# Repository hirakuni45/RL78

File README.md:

RL78
=========

[Japanese](READMEja.md)

## RL78 directories, overview, etc.

This is a program by RL78 and its compiler, rl78-elf-gcc,g++.
   
***For RL78 development, you can use the integrated development environment provided by Renesas Electronics, but for permanent use, you need to purchase the commercial version or generate your own.   
However, you need to purchase the commercial version to use it permanently, or you need to purchase the integrated development environment for RL78 because the generated binaries are limited to 64 Kbytes or less.   
Also, since it does not support C++, use gcc.   
We also emphasize the convenience of development on multiple platforms, such as Mac OS-X and Linux.   
I can also use [Open Source Tools for Renesas](https://llvm-gcc-renesas.com/)'s development tools, which require registration, but they don't fit my development style.   
I don't like IDEs very much. ***
   
Currently, I mainly provide headers, related libraries, etc. for "R5F100L" (G13 group).
   
R5F100LCAFB (FLASH: 32K, RAM: 2K, DATA-FLASH: 4K) @250 yen   
R5F100LEAFB (FLASH: 64K, RAM: 4K, DATA-FLASH:4K) @290 yen   
R5F100LGAFB (FLASH:128K, RAM:12K, DATA-FLASH:8K) @340 yen (conversion board already mounted @420 yen)   
R5F100LJAFB (FLASH:256K, RAM:20K, DATA-FLASH:8K) @400 yen   

@xxx is [reference price for Akizuki Denshi sales](http://akizukidenshi.com/catalog/c/crl78g13/)
   
The project consists of Makefile, related headers, and source code, and is composed of dedicated startup routines, linker scripts
It consists of a dedicated startup routine and a linker script.
Therefore, no dedicated boot program or loader is required, and the binaries you create can be executed as is.   
This means that you can run your application as is, without the need for a dedicated boot program or loader.
The entire process from the hardware reset to the device and your application running is detailed and easy to understand.   

***The most common case is that the compiler has been modified to switch functions dynamically, internally. ***   
***You can build a practical environment with only gcc and make without such a step. ***   
   
For device I/O operations, a template class library composed in C++ is used, and dedicated headers and class libraries for various devices are prepared.   
We are constantly improving and researching to realize highly functional and flexible operations with minimal implementation.   
We are looking for class libraries for unknown devices. (Must be able to provide under MIT license)   
E-Mail: hira@rvf-rc45.net

## RL78 Project List

|directory|contents|
|---|---|
|rl78prog|Programming tool to write programs to RL78 flash|
|G13|G13 group, linker scripts, device definition files|
|common|RL78 shared classes, small class library, utilities|
|chip|control classes for various devices, etc.||
|ff12a|"FatFS 0.12a" framework created by ChaN, and RL78/G13 SPI|
|KiCAD_Lib|Parts library for KiCAD|
|data_flah_lib|GR-Cotton/GR-Kurumi data/flash operation library|
|FIRST_sample|Super simple sample (blinking LED) for RL78/G13 devices|
|SOFT_DELAY_sample|Software timer sample for RL78/G13 devices|
|UART_sample|Serial communication sample for RL78/G13 devices|
|ARITH_sample|RL78/G13 Four arithmetic operations sample (receive and calculate mathematical expression by string)|
|ADC_sample|RL78/G13 internal A/D conversion sample|
|ADC_SWITCH_sample|RL78/G13 series switch (four rows) A/D conversion sample|
|THERMISTOR_sample|RL78/G13 Thermistor temperature display sample (using A/D conversion)|
|TOUCH_sample|RL78/G13 touch switch, sample|
|DATA_FLASH_sample|RL78/G13 Data flash sample (read, write, erase)
|INTERVAL_TIMER_sample|RL78/G13 internal 12-bit, interval timer samples|
|INTERVAL_TIMER_TAU_sample|RL78/G13 TAU use interval timer sample|
|EEPROM_sample|RL78?G13 EEPROM I2C Read/Write sample|
|DS3231_sample|RL78/G13 DS3231 I2C Real Time Clock time display and setting sample|
|DS1371_sample|RL78/G13 DS1371 I2C Real Time Clock time display, setting sample|
|BMP180_sample|RL78/G13 BMP180 I2C Pressure/Temperature sensor reading and display sample|
|VL53L0X_sample|RL78/G13 VL53L0X I2C Time-of-Flight distance sensor, sample|
|PWM_sample|RL78/G13 TAU use PWM output sample| 
|SDC_sample|RL78/G13 SD card operation sample (SD card root directory list)||
|WAV_PLAYER_sample|RL78/G13 WAV file playback sample (8-bit output by PWM modulation, up to 48KHz/16bits)
|VS1063_PLAYER_sample|RL78/G13 VS1063 Audio Decoder Playback sample
|LCD_DOT_sample|RL78/G13 ST7565(R)/SSD1306 SPI LCD controller, graphics display sample|
|MAX6675_sample|RL78/G13 MAX6675 SPI K thermocouple, temperature display sample|
|MAX7219_sample|RL78/G13 MAX7219 SPI LED display sample|

### Enable/Disable FatFS LFN   
The SD card file system "fatfs" uses "LFN" (long file name) as standard and displays UTF-8 is used as standard.    (UTF-8 and Shift-JIS conversion tables are available.)   
This requires a device of at least 128KB.   
This consumes a lot of memory. If you do not need it, set "_USE_LFN" in "ff12a/src/ffconf.h" to "0" and compile it.   
If you do not need it, you can compile the file with "_USE_LFN" set to "0" in "ff12a/src/ffconf.h" and the string code will be OEM, (ShiftJIS for CP932), with minimal Long file names are also disabled, and 8.3 format is used.   
   
## Preparation of RL78 development environment (Windows, MSYS2)
   
 - On Windows, install the MSYS2 environment beforehand.
 - There are three different MSYS2 environments: msys2, mingw32, and mingw64. 

 - Upgrading msys2

````shell
   pacman -Sy pacman
   pacman -Syu
````

 - Reopen the console. (You should see a message telling you to reopen the console.)

```shell
   pacman -Su
```
 - The update will be performed multiple times, and you must follow the console's instructions.
 - You will need to reopen the console multiple times.

 - Install gcc, texinfo, gmp, mpfr, mpc, diffutils, automake, zlib tar, make, unzip commands, etc.

````shell
   pacman -S gcc
   pacman -S texinfo
   pacman -S mpc-devel
   pacman -S diffutils
   pacman -S automake
   pacman -S zlib
   pacman -S tar
   pacman -S make
   pacman -S unzip
   pacman -S zlib-devel
````
  
 - Install git commands

```shell
   pacman -S git
```

---

## Preparation of RL78 development environment (OS-X)

 - For OS-X, install macports beforehand. (Brew is not recommended due to its inflexibility.)
 - (Depending on the OS-X version, you may need to install X-Code, Command Line Tools, etc. beforehand.)

 - Upgrading macports

```shell
   sudo port -d self update
```

 - As you probably know, in OS-X, llvm is initially invoked by gcc calls.
 - However, llvm is currently unable to build gcc cross-compilers.
 - So, we will install gcc with macports, and we will use the version 5 series.

```shell
   sudo port install gcc5
   sudo ln -sf /opt/local/bin/gcc-mp-5 /usr/local/bin/gcc
   sudo ln -sf /opt/local/bin/g++-mp-5 /usr/local/bin/g++
   sudo ln -sf /opt/local/bin/g++-mp-5 /usr/local/bin/c++
```

 - You may need to reboot.
 - Just to make sure.

```shell
   gcc --version
```
   
```shell
   gcc (MacPorts gcc5 5.4.0_0) 5.4.0
   Copyright (C) 2015 Free Software Foundation, Inc.
   This is free software; see the source for copying conditions.
   warranty; not even for MERCHANTABILITY or FITNESS FOR A PARTICULAR PURPOSE.
```
   
 - Install texinfo, gmp, mpfr, mpc, diffutils, automake commands, etc.

```shell
   sudo port install texinfo
   sudo port install gmp
   sudo port install mpfr
   sudo port install libmpc
   sudo port install diffutils
   sudo port install automake
```

---
## Preparation of RL78 development environment (Ubuntu)

Since there are multiple Linux environments, I will write about the "Ubuntu 16.04 LTS" environment here.

 - Install texinfo, gmp, mpfr, mpc, diffutils, automake commands, etc.

```shell
   sudo apt-get install texinfo
   sudo apt-get install libgmp-dev
   sudo apt-get install libmpfr-dev
   sudo apt-get install libmpc-dev
   sudo apt-get install diffutils
   sudo apt-get install automake
   sudo apt-get install zlib1g-dev
```

---
## Build RL78 development environment

 - Use gcc-4.9.4 as the compiler for RL78 (rl78-elf-gcc,g++).
 - Download binutils-2.25.1.tar.gz
 - Download gcc-4.9.4.tar.gz
 - Download newlib-2.2.0.tar.gz

---
   
#### build binutils-2.25.1

```shell
   cd
   tar xfvz binutils-2.25.1.tar.gz
   cd binutils-2.25.1
   mkdir rl78_build
   cd rl78_build
   ... /configure --target=rl78-elf --prefix=/usr/local/rl78-elf --disable-nls --with-system-zlib
   make
   make install OS-X,Linux: (sudo make install)
```

 - Pass /usr/local/rl78-elf/bin (edit .bash_profile and add the path)

```shell
   PATH=$PATH:/usr/local/rl78-elf/bin
```

 - Reopen the console.

```shell
   rl78-elf-as --version
```

 - Run the assembler commands to see if the path is valid.

#### build C Compiler

```shell
    cd
    tar xfvz gcc-4.9.4.tar.gz
    cd gcc-4.9.4
    mkdir rl78_build
	cd rl78_build
    ../configure --prefix=/usr/local/rl78-elf --target=rl78-elf --enable-languages=c --disable-libssp --with-newlib --disable-nls --disable-threads --disable-libgomp --disable-libmudflap --disable-libstdcxx-pch --disable-multilib --enable-lto --with-system-zlib
    make
    make install     OS-X,Linux: (sudo make install)
```
  
#### build newlib

```shell
    cd
    tar xfvz newlib-2.2.0.tar.gz
	cd newlib-2.2.0
    mkdir rl78_build
    cd rl78_build
    ../configure --target=rl78-elf --prefix=/usr/local/rl78-elf
	make
    make install     OS-X: (sudo make install)
```

 - Under Linux, the sudo command does not recognize the path to the binutils locally configured, so "make install" fails.   
Therefore, the following script should be written and executed.

```shell
#!/bin/sh
# file: rl78_install.sh

PATH=${PATH}:/usr/local/rl78-elf/bin
make install
```
   
```shell
    sudo rl78_install.sh
```
---  
#### build C++ Compiler

```shell
    cd
    cd gcc-4.9.4
    cd rl78_build
    ../configure --prefix=/usr/local/rl78-elf --target=rl78-elf --enable-languages=c,c++ --disable-libssp --with-newlib --disable-nls --disable-threads --disable-libgomp --disable-libmudflap --disable-libstdcxx-pch --disable-multilib --enable-lto --with-system-zlib
    make
    make install     OS-X,Linux: (sudo make install)
```
   
---
   
# Attention
   
In OS-X and Linux, remove the optimization option "-flto" set in the "Makefile" when building each project.   
Remove the optimization option "-flto" from the "Makefile" when building each project.   
   
Otherwise, an executable binary that does not work will be generated.   
This does not happen when building with *MSYS2.
   
Specifically, no information in the section containing unreferenced function addresses, etc., is output.   
We are currently investigating a workaround.   
We are currently investigating a workaround.   

At present, there is little benefit to be gained from "-flto", so for safety reasons, we have decided to build without this option in all environments.   
option in all environments to be safe.   
   
---

## Get source code for RL78 projects

```shell
   git clone https://github.com/hirakuni45/RL78.git
```
   
- Compile all projects

```shell
   sh all_project_build.sh
```
   
--- 

## How to write a program to an RL78/G13 device

- There are several ways to do this, but the easiest and least expensive way is to write using a serial interface.
- However, it is not possible to connect directly like R8C.
- Three (5) signals from the serial interface must be connected to the microcontroller with appropriate conversion circuitry.
- Using a USB serial conversion module or the like, it is easy to obtain a power supply.

### (Akizuki Denshi, serial conversion module) http://akizukidenshi.com/catalog/g/gK-06894/   
(1) RXD Serial receive   
(2) TXD Serial transmit   
(3) RTS Hardware control signal   
(4) VCC Power supply (5V or 3.3V)   
(5) GND Power supply 0V   

Since only a limited current can be drawn from 3.3V, it is recommended to use a regulator.   
A conversion adapter that can take out the RTS signal is required.   
We do not recommend cheap modules made in China because they do not have RTS or their quality is not stable.   
Only those who understand and can deal with these issues should use these modules.  

- Refer to rl78prog/KiCAD/ for the schematic, which has a simple write circuit.
- It seems that the above circuit can also be written using Renesas Flash Programmer (not confirmed).
- The regular circuit can be downloaded from the Renesas Electronics homepage.
- (Of course, you can also write with Renesas Electronics E1, E2, and emulators sold by Renesas Electronics.
- Connect to “P40/TOOL0 (5)” and “/RESET (6)” of RL78/G13 (64-pin product)
- Serial communication is often used in the development process, so it is convenient to be able to switch between them with a switch.
- A reference circuit for switching is provided in “rl78prog/KiCAD”.
- It is possible to write with the serial conversion circuit at very high speed, so it may be better to consider the cost of purchasing a new E1 for the RL78.
- Currently, the rl78prog can only be written to in a Windows environment.
- In that case, please consider using Renesas Flash Programmer.

## Building RL78 flash programmer

- boost_1_74_0" is required to build rl78prog. (For MSYS2/MSYS environment)
- We have not investigated other USB serial chips.
- Since boost uses only headers, it does not need to be built.
- Boost_1_74_0 should be extracted to the root of the C drive.
 
```shell
    cd /c/
    tar xfvz boost_1_74_0.tar.gz
    cd boost_1_74_0
    ls
boost/     boost-build.jam  bootstrap.sh*  index.html  libs/            README.md  tools/
boost.css  boostcpp.jam     doc/           INSTALL     LICENSE_1_0.txt  rst.css
boost.png  bootstrap.bat    index.htm      Jamroot     more/            status/
```

 - Build rl78prog (MSYS2)
 - Place the built executable in /usr/local/bin.

```shell
    cd rl78prog
    make
    make install
　　Put the path to /usr/local/bin.
```
 - Edit rl78_prog.conf and set the COM port and baud rate.
 - Only "115200", "500000", and "1000000" baud rates are supported due to the RL78 specification and termios limitations.
 - Equivalent to /dev/ttyS10 -> COM11. (+1 to the number)
 - rl78prog/KiCAD/ contains reference circuits for RL78 programmer (writing machine), etc.

 - Serial devices confirmed to work   
   
||FT231X|CP2102|CH340|
|---|:---:|:---:|:---:|
|Windows |○ |○ |△ |
|OS-X |× |× |△ |
|Linux |x |x |△ |△ |
   
○：Confirmed operation, △：Unconfirmed, ×：Malfunction   

Although the writing software is multi-platform compatible, currently it can only be used in a Windows environment.   
The writing software is multi-platform, but currently only works in Windows environment.   
  
---
## RL78-specific limitations and solutions
   
RL78 is classified as a 16-bit microcontroller, but strictly speaking, it is not.   
Basically, it is no different from an 8-bit microcontroller, and can be said to be an 8-bit microcontroller with a large address space.   
When writing C or C++ programs, it is important to note that the pointer is basically 16 bits, and only 64K bytes of space can be accessed.   
In special cases, the __far pointer can be used, but it is not efficient.   
In special cases, the __far pointer can be used, but it is less efficient and can be used only for special purposes.   
In the case of using FatFS, the conversion table between UTF-8 and CP932 can be placed in the latter half of the ROM Flash area, and the __far_ pointer can be used to access the 64K byte space.   
The program counter is extended to 20 bits.   
   
The program counter is extended to 20 bits and operates in a 1M-byte area.   

The RAM and I/O areas are assigned to 0xF0000 and after, and access to these areas requires the use of an addressing address whose upper 4 bits are fixed.   
The compiler can access a 20-bit area by using an addressing mode in which the upper 4 bits are fixed and a 16-bit access is performed.   
The compiler acts as if it is accessing a 20-bit area, but in fact it can only access a 16-bit area.   
In reality, only a 16-bit area can be accessed.   
For more information, see the explanation of "Mirror Area.   
   
Renesas Electronics has not released the documentation required to write to the internal data flash.   
Renesas Electronics does not provide the necessary documentation for writing to the internal data flash, nor does it provide a data flash library for gcc.   
~~Therefore, it is not possible to use the internal data flash in the current situation.~~  
~~If you want to store some data, you can use EEPROM with I2C connection.~~   
GR-Cotton and GR-Kurumi use RL78/G13, and the WEB compiler is gcc.   
The situation has changed since we found out that the RL78/G13 is used in GR-Cotton and GR-Kurumi, and that the data flash library (gcc version of PFDL T4) can be used.   
Now, data flash operation can be performed normally.   
   
## How each project works and secrets
   
 - Currently, the project may not be well maintained and may be committed in a halfway state.   
 - If it does not work, please contact us as there may be a problem with the program.   
 - Refer to the list of each project and go to the directory of the project.   
 - Each project defaults to "R5F100LGAFB" (ProgramFlash: 128KB, RAM: 12KB, DataFlash: 8KB).
 - It can be changed to other devices in the Makefile. The work RAM sizes are different and must be matched.
 - Basically, the device operates at 32 MHz using an internal oscillator.
 - If you want to change the operating frequency, you need to specify F_CLK in the Makefile at the same time.   
 - Currently, the software delay only supports 32MHz.   
 - If you want to use a more accurate clock, you can connect an external crystal and enable external oscillation.
 - However, the software only supports crystals up to 20 MHz or external clocks.   
 - The operating frequency setting at startup is done in common/option_bytes.c.   
 - Since C++ templates are used extensively, binaries tend to be large.   
 - If you want to optimize the binary with priority on size, specify "-Os" to make the binary smaller.   
 - When "-Os" is specified, *"-flto" should not be used in the current situation. (It seems to be a bug in gcc.)   
 - R5F100LGAFB" is available soldered on a conversion board at a reasonable price. (Akizuki Denshi)   
 - Please refer to the RL78/G13 hardware manual for wiring.
 - Basically, just connect the power supply and appropriate bypass capacitors.   
 - If you require special (complicated) connections, KiCAD project files are available.     
   
### Interrupt Precautions

 - UART, timers, etc., interrupt entries, be up-to-date!
 - Basically, the base entries are defined in vect.h and vect.c.
 - On the main side, use the entries defined in the base as an implementation of C language functions.
 - On the main side, the interrupt entry always includes "renesas.hpp".
 - The "renesas.hpp" contains the definitions of the attributes of the interrupt entries.
 - Without the definition in "renesas.hpp", the interrupt entry will function as a normal function and will not work.
 - For functions defined using "__attribute__((weak))", the redefinition side takes precedence.
 - The header side has "INTERRUPT_FUNC;" appended and functions as an interrupt handler.
 - The interrupt task in each driver template is a normal function since it is assumed to be called by the interrupt handler.
 - Note that typoing the entry name will not cause an error, it will just exist as an invalid function.
 - **Interrupt handler typos, problems caused by forgetting to include "renesas.hpp" are difficult to find. **
   
### Notes on data flash operations

 - As a standard, the link file is made on the assumption that the Renesas PFDL-T4 library is used.
 - For details, please refer to the documents related to [PFDL-T4](https://www.renesas.com/ja-jp/software/D3016252.html).
 - The work area of the library is reserved in the second half of RAM. (136 bytes)
 - If you do not use the library and want a little RAM, you can modify the link file.
 - Be careful when modifying the gcc link file.
   
### incorporation and configuration of common/syscalls.c

 - syscalls contains the required POSIX implementation. (not all).
 - The main ones are stdout and stdin. （The main ones are stdout, stderr, and stdin.)
 - In addition, file operations are included if the SD card file system is incorporated.
 - Standard I/O can be assigned as serial I/O in main.cpp.
 - To do so, implement "sci_putch, sci_getch".
 - To incorporate the SD file system, define the interface with FatFS.
 - Refer to "main.cpp of SDC_sample".
 - OPEN_MAX_" in "syscalls.c" limits the number of files that can be opened simultaneously.
 - Currently, up to 3 files can be open at the same time.
 - The number can be increased, but this will reduce the work RAM area.
 - When using the SD file system, a device with a FLASH area of 128K or more is recommended.
   
### Using format instead of printf

 - By including syscalls.c, you can automatically use the printf function.
 - However, it is not recommended.
 - The printf argument is stack-based, and inconsistencies can lead to very fickle behavior.
 - Basically, in C++, there is no reason to use printf, which is convenient but highly dangerous.
 - Instead, use utils::format.hpp, which offers similar functionality and convenience.
 - Instructions are included in the examples.
 - Instead of scanf, utils::input.hpp is provided.
   
---

 - Build. (It will automatically generate the dependency rules for you.)

```shell
    make
```

 - write the program (requires rl78_prog)

```shell
    make
    make run
```

---

## create new project

 - Create a new project directory.
 - Copy "Makefile" and "main.cpp" from UART_sample and other files.
 - Rewrite the necessary parts of the Makefile for your own project.
 - You can add your own source code name to the source code path in the Makefile.
 - In the Makefile, the "Dependency Rule" is important, but it is generated automatically.
   
---

## File overview

|file name|Spec|
|---|---|
|G13/R5F100LCAFB.ld|Linker script for R5F100LCAFB ( 32K/ 2K/4K)|
|G13/R5F100LEAFB.ld|Linker script for R5F100LEAFB (64K/ 4K/4K)|
|G13/R5F100LGAFB.ld|Linker script for R5F100LGAFB (128K/12K/8K)|
|G13/R5F100LJAFB.ld|Linker script for R5F100LJAFB (256K/20K/8K)|
|G13/readme.txt|Linker script overview|
|G13/adc.hpp|A/D converter definition|
|G13/dma.hpp|DMA controller definition|
|G13/iica.hpp|IICA (I2C) definition|
|G13/intr.hpp|Interrupt control relation definition|
|G13/port.hpp|Port relation definition|
|G13/sau.hpp|Serial Array Unit definition|
|G13/system.hpp|system-related definition|
|G13/tau.hpp|timer array unit definition|
|G13/timer.hpp|12-bit interval timer definition|
   
---

|file name|Spec|
|---|---|
|chip/chip_list.txt|chip list|
|chip/BMP180.hpp|I2C BOSHE BMP180 temperature and pressure sensor driver|
|chip/DS3231.hpp|I2C Maxim DS3231 RTC Real Time Clock Driver|
|chip/DS1371.hpp|I2C Maxim DS1371 RTC real-time clock driver (32-bit binary counter)|
|chip/EEPROM.hpp|I2C connection EEPROM driver|
|chip/MPU6050.hpp|I2C InvenSense Accelerometer, Gyro sensor driver|
|chip/ST7565.hpp|SPI LCD single color, dot matrix driver|
|chip/SSD1306.hpp|SPI OLED single color, dot matrix driver|
|chip/UC1701.hpp|SPI LCD single color, dot matrix driver|
|chip/VS1063.hpp|SPI MP3 / OGG VORBIS encoder, decoder driver|
|chip/NTCTH.hpp|Analog thermistor linear completion template|
|chip/VL53L0X.hpp|I2C Time-of-Flight distance sensor driver|
|chip/MAX6675.hpp|SPI K Thermocouple Temperature Sensor Driver|
|chip/MAX7219.hpp|SPI LED driver|
   
---

|file name|Spec|
|---|---|
|common/start.s|hardware reset, initialization|
|common/init.c|main initialization|
|common/option_bytes.hpp|option byte setting|
|common/vect.h|hardware vector definition|
|common/vect.c|hardware vector settings|
|common/time.h|time function definition (reduced version of posix time.h)|
|common/time.c|time function implementation (reduced version of posix time.c)|
|common/io_utils.hpp|I/O control template utilities|
|common/adc_io.hpp|A/D conversion control template|
|common/basic_arith.hpp|Four arithmetic input class|
|common/bitset.hpp|bit-packed simple template class (reduced set of std::bitset)|
|common/command.hpp|line input template|
|common/csi_io.hpp|CSI(SPI) conversion control template|
|common/delay.hpp|software delay (32 MHz operation, in microseconds)|
|common/fifo.hpp|First-in first-out buffer|
|common/filer.hpp|file selection for bitmap graphics|
|common/font6x12.hpp|6x12 pixel, ASCII font class (definition)|
|common/font6x12.cpp|6x12 pixel, ASCII font class (entity)|
|common/format.hpp|string formatting template|
|common/iica_io.hpp|IICA input/output template|
|common/itimer.hpp|interval timer control template|
|common/kfont12.bin|12-pixel Kanji font bitmap data|
|common/kfont12.hpp|12-pixel Kanji font class|
|common/monograph.hpp|bitmap graphics control class|
|common/port_utils.hpp|port utilities|
|common/sdc_io.hpp|SD card control class|
|common/string_utils.hpp|string utilities (code conversion, etc.)|
|common/switch_man.hpp|switch management classes|
|common/task.hpp|task control (disabled task class)|
|common/tau_io.hpp|Timer control template|
|common/uart_io.hpp|Serial communication input/output (UART)|
   
---

Translated with www.DeepL.com/Translator (free version)

---
License

MIT

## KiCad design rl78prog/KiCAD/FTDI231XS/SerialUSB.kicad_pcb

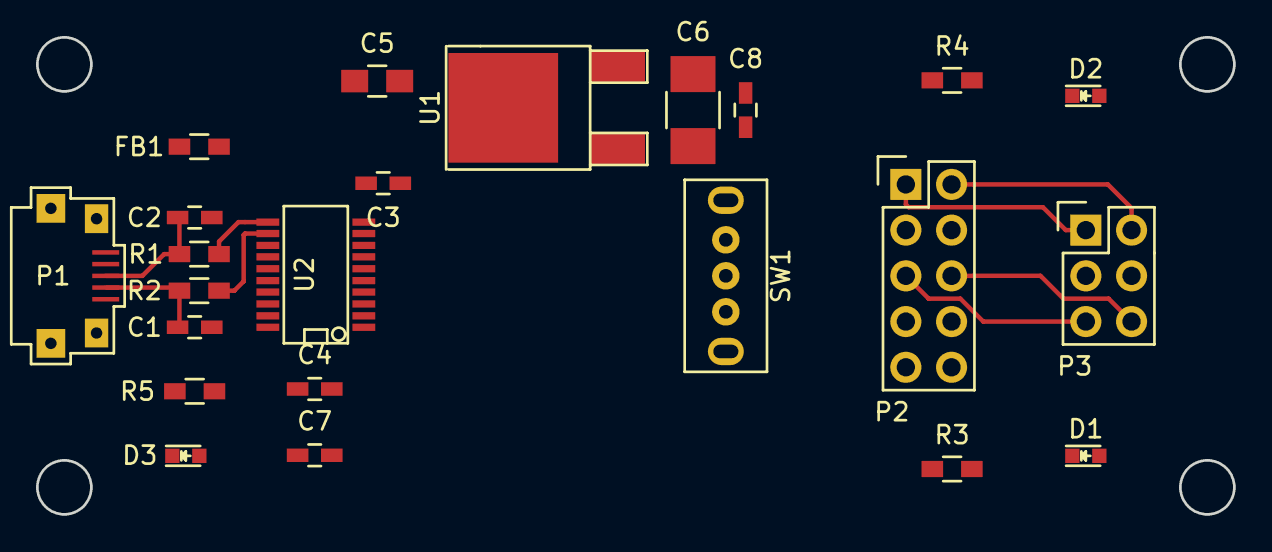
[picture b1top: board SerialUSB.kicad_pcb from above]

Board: 2 copper layers, 66.5 x 26.5 mm, 23 parts (0 on the bottom side), 23 nets.

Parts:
C1, C2: 47pF; C_0603_HandSoldering
C3, C4, C7, C8: 0.1uF; C_0603_HandSoldering
C5: 4.7uF; C_0805_HandSoldering
C6: 22uF; C_1210_HandSoldering
D1: GREEN; LED_0603
D2: RED; LED_0603
D3: BLUE; LED_0603
FB1: BLM18PG471SN1D; R_0603_HandSoldering
P1: USB_OTG; HRS-MICRO-USB-B
P2: CONN_02X05; Pin_Header_Straight_2x05
P3: CONN_02X03; Pin_Header_Straight_2x03
R1, R2: 27; R_0603_HandSoldering
R3, R4: 1.2K; R_0603_HandSoldering
R5: 760; R_0603_HandSoldering
SW1: 3P-SW; SS-12D01-VG4
U1: NJU7223DL1-33; TO-252-2Lead
U2: FT231XS; SSOP-20

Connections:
+5V: C3.1, C5.2, D3.2, FB1.1, R3.1, R4.1, SW1.3, U1.2, U2.15
//CTS: P2.6, P3.6, U2.9
//DCD: P2.9, U2.8
//DSR: P2.8, U2.7
//DTR: P2.7, U2.1
//RI: P2.10, U2.5
//RTS: P2.5, P3.5, U2.2
/RXD: P2.1, P3.1, U2.4
/TXD: P2.2, P3.2, U2.20
GND: C1.1, C2.2, C3.2, C4.2, C5.1, C6.1, C7.2, C8.2, P1.5, P2.3, P3.3, R5.2, U1.3, U2.6, U2.16
unnamed: C1.2, P1.2, R2.2
unnamed: C2.1, P1.3, R1.2
unnamed: C4.1, U2.13, U2.14
unnamed: C6.2, C7.1, SW1.1, U1.1
unnamed: C8.1, P2.4, P3.4, SW1.2, U2.3
unnamed: D1.1, U2.17
unnamed: D1.2, R3.2
unnamed: D2.1, U2.10
unnamed: D2.2, R4.2
unnamed: D3.1, R5.1
unnamed: FB1.2, P1.1
unnamed: R1.1, U2.11
unnamed: R2.1, U2.12

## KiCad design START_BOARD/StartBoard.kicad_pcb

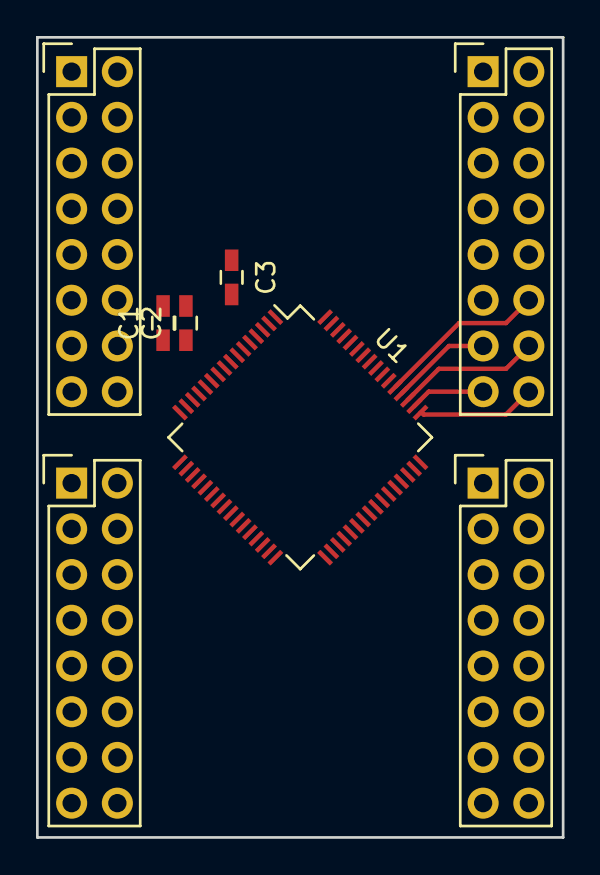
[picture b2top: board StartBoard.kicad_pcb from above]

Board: 2 copper layers, 29.2 x 44.5 mm, 8 parts (0 on the bottom side), 62 nets.

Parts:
C1, C2: 0.1uF; C_0603_HandSoldering
C3: 1uF; C_0603_HandSoldering
P1, P2, P3, P4: CONN_02X08; Pin_Header_Straight_2x08
U1: R5F100LxAFB; LQFP-64_10x10mm_Pitch0.5mm

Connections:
+3V3: C1.1, C2.1, P1.15, P1.16, U1.15, U1.16
//RESET: P1.6, U1.6
/P00: P3.3, U1.62
/P01: P3.4, U1.61
/P02: P3.5, U1.60
/P03: P3.6, U1.59
/P04: P3.7, U1.58
/P05: P2.15, U1.31
/P06: P2.14, U1.30
/P10: P4.4, U1.46
/P11: P4.3, U1.45
/P12: P4.6, U1.44
/P13: P4.5, U1.43
/P14: P4.8, U1.42
/P15: P4.7, U1.41
/P16: P4.10, U1.40
/P17: P4.9, U1.39
/P20: P3.9, U1.56
/P21: P3.10, U1.55
/P22: P3.11, U1.54
/P23: P3.12, U1.53
/P24: P3.13, U1.52
/P25: P3.14, U1.51
/P26: P3.15, U1.50
/P27: P3.16, U1.49
/P30: P2.16, U1.32
/P31: P2.5, U1.21
/P40: P1.5, U1.5
/P41: P1.4, U1.4
/P42: P1.3, U1.3
/P43: P1.2, U1.2
/P50: P4.15, U1.33
/P51: P4.16, U1.34
/P52: P4.13, U1.35
/P53: P4.14, U1.36
/P54: P4.11, U1.37
/P55: P4.12, U1.38
/P60: P2.1, U1.17
/P61: P2.2, U1.18
/P62: P2.3, U1.19
/P63: P2.4, U1.20
/P70: P2.13, U1.29
/P71: P2.12, U1.28
/P72: P2.11, U1.27
/P73: P2.10, U1.26
/P74: P2.9, U1.25
/P75: P2.8, U1.24
/P76: P2.7, U1.23
/P77: P2.6, U1.22
/P120: P1.1, U1.1
/P121: P1.11, U1.11
/P122: P1.10, U1.10
/P123: P1.8, U1.8
/P124: P1.7, U1.7
/P130: P3.8, U1.57
/P137: P1.9, U1.9
/P140: P3.1, U1.64
/P141: P3.2, U1.63
/P146: P4.1, U1.47
/P147: P4.2, U1.48
GND: C1.2, C2.2, C3.2, P1.13, P1.14, U1.13, U1.14
unnamed: C3.1, U1.12

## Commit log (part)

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2016-10-09 fix optimize lto
2016-10-09 update ioctrl setting
2016-10-09 update system define port name
2016-10-09 update USB serial driver
2016-10-09 update platform
2016-10-11 update voltage
2016-10-11 update sequrity command
2016-10-11 fix help
2016-10-11 comment out security set
2016-10-11 update unsigned value
2016-10-18 update compile option
2016-10-18 rename a file
2016-10-18 remove a file
2016-10-18 update optimize
2016-10-18 update device name
2016-11-09 new file
2016-11-10 fix BMP180/BMP280 presure/altitude
2016-11-10 update altutude
2016-11-10 update comment
2016-11-11 update pressure
2016-11-11 update c++14 binary literal
2016-11-16 add new file
2016-11-16 update single port class
2016-11-16 fix shift API
2016-11-18 update port direction
2016-11-18 update include path
2016-11-20 update ST7565 interface
2016-11-20 update interface
2016-11-20 update parts
2016-11-20 update circuit
2017-01-15 fix compare length
2017-02-01 update operator
2017-02-01 add conversion status
2017-09-20 new file (data_flash library)
2017-09-20 update PFDL_COD for text section
2017-09-20 update copyright
2017-09-20 remove *.a file
2017-09-20 new project
2017-09-21 update copyright text
2017-09-21 update interrupt functions
2017-09-22 update interrupt handler
2017-09-22 cleanup
2017-09-22 update test code for LED blink
2017-09-24 update FDL-T04 area
2017-09-24 update excecption state
2017-09-24 update startup option
2017-09-24 update reset after initializations
2017-09-24 add pfdl.o
2017-09-24 update const
2017-09-24 update flash management
2017-09-24 fix erase status
2017-09-24 update interrupt task
2017-09-24 fix zero divide exceptions
2017-09-24 update device selector
2017-09-24 update device sig
2017-09-25 fix TMxx interrupt entry attribute
2017-09-25 fix interrupt handler
2017-09-25 update section
2017-09-25 fix include path for interrupt attribute
2017-09-25 fix inteerupt entry for A/D
2017-09-25 update open file max
2017-09-26 update def win port
2017-09-26 update RL78 line ctrl
2017-09-26 update OS-X serial port
2017-09-26 update A/D temp
2017-09-26 update option bytes
2017-09-26 update interrnal temp
2017-09-26 update serial speed
2017-09-27 update help text
2017-09-27 add api (nano_second)
2017-09-27 update port init
2017-09-28 add API
2017-09-28 cleanup include path
2017-09-28 update pointer type
2017-09-28 update port optional class
2017-09-28 update serial management
2017-09-28 update positive/negative trigger
2017-09-28 update interrupt attribute
2017-09-28 update L1C device
2017-09-29 fix RO area start address
2017-09-29 update multi device
2017-09-29 update L1C
2017-09-30 update UART interrupt handle
2017-09-30 update UART interrupt
2017-09-30 update UART
2017-09-30 fix peripheral enable management
2017-09-30 update interrupt management
2017-09-30 update UART request API
2017-09-30 change namesapce to class
2017-09-30 change namespace to class
2017-09-30 update TAU enableing
2017-09-30 update interrupt TAU
2017-09-30 update peripheral
2017-09-30 update TAU interrupt handling
2017-09-30 update UART2/UART3 interrupt vector
2017-10-02 update TAU port manage
2017-10-03 fix include path (multi device)
2017-10-03 update TAU manage
2017-10-03 update manage
2017-10-03 update interrupt management for IICA
2017-10-03 update I2C
2017-10-03 update IICA port
2017-10-03 update IICA interrupt handle
2017-10-05 update 40pin device UART port config
2017-10-06 update switch manage
2017-10-06 update bit position manage
2017-10-09 update enum class
2017-10-09 update enum class for switch_man
2017-10-23 update I2C test
2017-10-23 update initialization
2017-10-23 update slave/master
2017-10-23 update input select
2017-10-25 update Audio interface (add DSP, RJF, LJF)
2017-10-27 update start param
2017-10-28 update version 0.29, LED control at power off, MUTE control at power off
2017-11-06 update clock generations
2017-11-06 version 0.30
2017-11-07 update port manage
2017-11-07 update port ctrl
2017-11-08 update input/output typedef
2017-11-08 update template paramter
2017-11-10 cleanup switch_man
2017-11-10 fix peripheral enable status
2017-11-10 update peripheral status check
2017-11-10 update SPI initialize
2017-11-10 typo version 0.11
2017-11-13 update I2S interface initializations
2017-11-15 update beta-01
2017-11-15 update Version 0.31 BETA-01
2017-11-16 update clock divider
2017-12-13 update noise fix
2017-12-13 update basic set
2018-02-13 update: version 0.13
2018-02-13 update: sampling 384FS to 256FS for 44.1KHz
2018-02-13 update: TXD-CH output delay, MUTE delay, version 0.34
2018-02-13 update: version 0.34
2018-02-13 add: new file
2018-02-19 fix: PCM1772/PD pin assign
2018-02-19 update: version 0.14
2018-03-18 fix: UART3 interrupt flag
2018-03-18 update: PCM1772 startup mode
2018-03-18 update: PORT config type (template param)
2018-03-18 update: cleanup
2018-03-18 update: SD1x, SD2x manage, send channel data for UART1 and 2, channel manage
2018-03-18 update: version 0.16
2018-03-18 update: default channel
2018-03-18 update: version 0.17
2018-03-22 update: flash memory size manage for linker script
2018-03-22 update: add data flash size
2018-03-22 update: flash size manage
2018-03-22 update: append data flash size
2018-03-22 update: device siguneture define
2018-03-26 update: version 0.35
2018-03-27 update: add mute API
2018-03-27 fix: return value, other
2018-03-27 update: Version 0.36
2018-04-04 update: version 0.37
2018-04-04 update: version 0.18
2018-04-08 update: version 0.38
2018-04-13 update: RINV
2018-04-13 update: version 0.19
2018-04-13 update: mute enable/disable
2018-04-13 update: version 0.39
2018-04-24 update: input selector change
2018-04-24 update: new API
2018-04-24 update: version 0.40
2018-04-26 update: add dither ctrl
2018-04-26 update: version 0.41
2018-05-31 fix: play audio at '<' command, remain time
2018-05-31 update: version 0.20 for RECVER
2018-07-03 fix: bit width for TMR/CKS
2018-07-03 update: change 32K to 64K cpu
2018-07-14 update: IR send, manage
2018-07-14 update: TAU for remocon
2018-07-14 update: REMOCON
2018-07-14 update: end of IR send to disable signal
2018-07-14 update: IR send manage
2018-07-16 update: IR term frame
2018-07-16 update: remocon manage
2018-07-16 update: IR recv manage
2018-07-16 update: RECV Version 0.21
2018-07-16 update: DMIC Version 0.42
2018-08-19 update: Version 0.22
2018-08-20 update: volume API
2018-08-20 fix: set_volume API name
2018-08-21 update: Version 0.23 for Reciver
2018-08-22 update: Reciver Version 0.24
2018-08-22 update: error collection, data stream manage
2018-08-22 update: DMIC Version 0.43
2018-08-27 fix: octal, binary sign bit
2018-08-28 update: version 0.45 for DMIC
2018-08-30 fix: octal mask
2018-11-23 add: a new file
2019-02-22 update: start_pwm output ctrl
2021-11-25 Update: boost path
2021-11-25 Update: boost install
2021-11-25 Add: a new directory for VSC
2021-11-28 Update: Defines the reality of the template class
2021-11-28 Update: new polycy handling
2021-11-28 Update: recv data timing loop delay
2021-11-28 Add: a new project
2021-11-28 Update: intellisense mode
2022-03-24 Update: attribute directory
2022-05-19 Update: git clone path
2022-06-12 Update: cleanup, translate english
2024-04-15 Update: code for gcc-13.2.0
2025-01-28 Update: fix boost path for rl78prog
